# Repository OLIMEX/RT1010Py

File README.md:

# RT10100Py
RT1010Py is Cortex-M7 running at 500Mhz MicroPython board

https://www.olimex.com/Products/MicroPython/RT1010-Py/open-source-hardware

The RT1010-Py can also be used together with its DevKit board 

https://www.olimex.com/Products/MicroPython/RT1010Py-DevKit/open-source-hardware

## Features
* MIMXRT1011DAE5A running at 500Mhz
* 128KB on board RAM
* 2MB SPI Flash
* Three UARTs
* Two hardware SPIs
* Two hardware I2Cs
* One hardware I2S
* Four PWM units with complementary outputs for push-pull drivers
* USB 2.0 OTG
* Micro SD card connector
* RTC with 32.768 kHz crystal
* RESET button
* BOOT button
* UEXT connector with 3.3V, GND, I2C, SPI, and UART
* Two GPIOs headers spaced at 22.86 mm (0.9”)
* Dimensions: (53.34 x 25.4)mm (2.1 x 1)”

## Library

The library must be copied on the MicroPython board before using some of the examples.

### MicroPython MIP Installer

On a WiFi capable plateform:

```
>>> import mip
>>> mip.install("github:OLIMEX/RT1010Py")
```

Or via the mpremote utility :

```
mpremote mip install github:OLIMEX/RT1010Py
```

### Manual installation

Copy all the files from __OLIMEX/RT1010Py/lib__ repository to your MicroPython board under __/lib__ directory.

## Documentation

Check the files in OLIMEX/RT1010Py/__DOCUMENTS__ for ressources:

* [RT101-0Py User Manual](DOCUMENTS/RT1010Py-user-manual.pdf) (pdf)
* [RT1010-Py PinOut](DOCUMENTS/RT1010-py-pinout.jpg) (jpg)
* [RT1010-py board](DOCUMENTS/RT1010-py-board.png) (png, for drawing circuit)
* and some other

Also check the RT1010Py-DevKit user manual at [OLIMEX/RT1010Py-DevKit repository](https://github.com/OLIMEX/RT1010Py-DevKit/tree/main)

## Licensee
* Hardware is released under Apache 2.0 Licensee
* Software is released under GPL3 Licensee
* Documentation is released under CC BY-SA 3.0

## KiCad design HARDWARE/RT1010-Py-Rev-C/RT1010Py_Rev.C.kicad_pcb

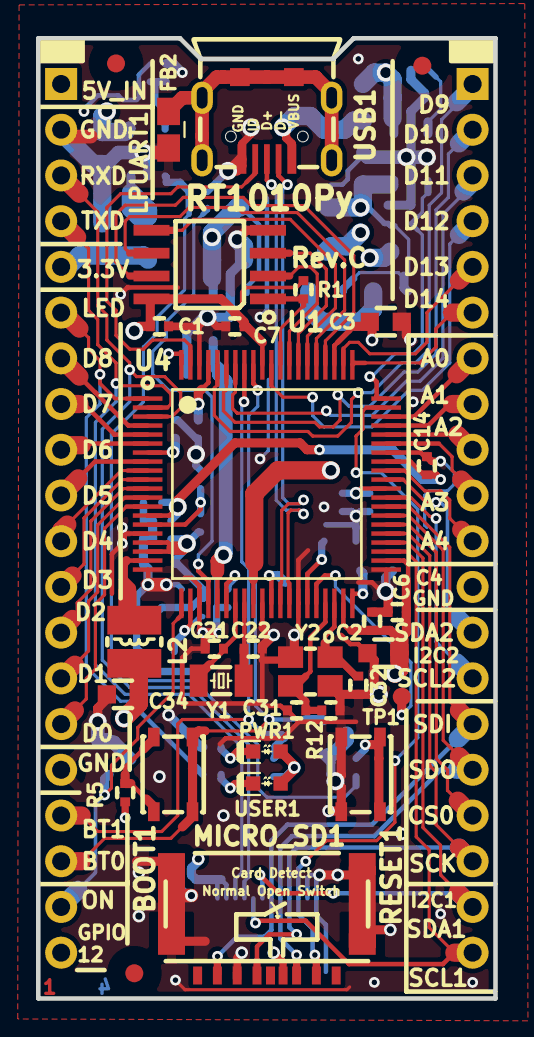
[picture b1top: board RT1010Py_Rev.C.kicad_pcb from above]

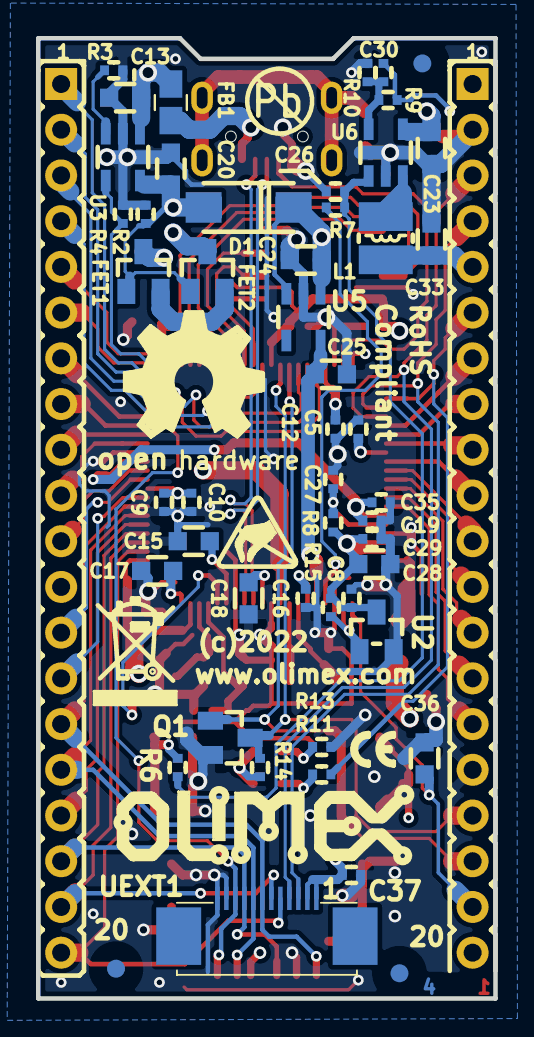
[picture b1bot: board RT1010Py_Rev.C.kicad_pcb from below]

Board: 4 copper layers, 25.4 x 53.3 mm, 89 parts (58 on the bottom side), 77 nets.

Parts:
Anty_Static: Val**; LOGO_ANTISTATIC_SMALL_4.5mmX2.8mm
BOOT1: YTS-A016-X
C1, C8, C37: 100nF/10V/20%/X5R/0402; C_0402_5MIL_DWS
C2, C3, C15, C17, C18, C24, C25, C33: 4.7uF/6.3V/0603; C_0603_5MIL_DWS
C4, C5, C6, C7, C9, C10, C12, C14, C16, C19, C26, C27, C29, C35: 220nF/+80-20%/10VDC/0402; C_0402_5MIL_DWS
C13, C20, C23: 10uF/6.3V/20%/X5R/0603; C_0603_5MIL_DWS
C21, C22, C30: 22pF/NP0/5%/0402; C_0402_5MIL_DWS
C28, C34: 22uF/6.3V/20%/X5R/0603; C_0603_5MIL_DWS
C31, C32: 33pF/50V/5%/C0G/0402; C_0402_5MIL_DWS
C36: NA; C_0603_5MIL_DWS
CON1, CON2: HN1X20; HN1x20
D1: 1N5822/(SS34)/SMA; SMA-KA
FB1, FB2: FB0805/600R/2A; L_0805_5MIL_DWS
FET1, FET2: WPM2015-3/TR; SOT23
FID1, FID2, FID3, FID4, FID5, FID6: Fiducial; Fiducial1x3
L1, L2: 2.2uH/NRS3015T2R2MNGH; CD32
MICRO_SD1: uSD(TFC-9P-1.7H); uSD(TFC-9P-1.xH(ATFFS150A01BR016))
OSH_Logo: LOGO_OPENHARDWARE_8x8
Olimex_Logo: OLIMEX_LOGO_TB
PB_Free: LOGO_PBFREE
PWR1: LED/Yellow/0603; LED_0603_KA
Q1: LMUN2211LT1G; SOT23
R1, R2, R4, R7, R11, R13: 10K/0402; R_0402_5MIL_DWS
R3: 10K/1%; R_0402_5MIL_DWS
R5, R6: 100R/0402; R_0402_5MIL_DWS
R8: 30K/0402; R_0402_5MIL_DWS
R9: 4.99K/1%; R_0402_5MIL_DWS
R10: 1.1K/1%; R_0402_5MIL_DWS
R12: 1M/0402; R_0402_5MIL_DWS
R14: 2.2K/0402; R_0402_5MIL_DWS
R15: 100K/0402; R_0402_5MIL_DWS
RESET1: YTS-A016-X
ReCycle: LOGO_RECYCLEBIN_1
Sign_CE_Small: CE_Sign_Small
TP1: TESTPAD; TP_SMD
U1: EN25QH16B-104HIP; SOIC-8_208mil
U2: VDA2710NTA(SOT-23); SOT-23
U3: SY6280AAC(SOT23-5); SOT-23-5
U4: MIMXRT1011DAE5A; LQFP-80_12x12mm_0.5_mm_pitch
U5: HX6211A332MR; SOT-23-5
U6: SY8089AAAC(SOT23-5); SOT-23-5
UEXT1: FPV-WZB21-12-LF
USB1: MISB-SWMM-5B-LF; USB-MICRO_MISB-SWMM-5B_LF
USER1: LED/Green/0603; LED_0603_KA
Y1: 32.768KHz/12.5pF/2P/1206; CM7V-T1A(Crystal_Package-1206_3.20x1.50x0.65mm)
Y2: 24MHz/20ppm/20pF/4P/3225; TSX-3.2x2.5mm_GND(3)

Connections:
+3V3: C1.1, C2.1, C3.1, C4.1, C5.1, C6.1, C7.1, C8.1, C9.1, C10.1, C28.1, C29.1, C30.1, C33.1, C37.1, CON1.5, L1.2, MICRO_SD1.4, PWR1.2, R1.1, R5.1, R8.2, R9.1, R14.1, R15.1, U1.8, U2.3, U4.7, U4.17, U4.18, U4.39, U4.42, U4.50, U4.63, U4.71, UEXT1.1, UEXT1.2, USER1.2
/5V_USB_OTG: C13.1, FB1.2, FET1.3, U3.1, U4.29
/BOOTSEL0: BOOT1.2, CON1.18, Q1.1, U4.72
/BOOTSEL1: CON1.17, Q1.3, R14.2, U4.73
/BUT_RESET: R6.2, RESET1.2
/GPIO2_IO00: CON2.1, U4.76
/GPIO2_IO01: CON2.2, U4.75
/GPIO2_IO02: CON2.3, U4.74
/GPIO2_IO05: CON2.4, U4.70
/GPIO2_IO12: CON2.5, U4.62
/GPIO2_IO13: CON2.6, U4.61
/GPIO_00: CON1.15, U4.13
/GPIO_01: CON1.14, U4.12
/GPIO_02: CON1.13, U4.11
/GPIO_03: CON1.12, U4.10
/GPIO_04: CON1.11, U4.9
/GPIO_05: CON1.10, U4.8
/GPIO_06: CON1.9, U4.6
/GPIO_07: CON1.8, U4.5
/GPIO_08: CON1.7, U4.4
/GPIO_11_LED: CON1.6, R11.2, U4.1
/GPIO_12: CON1.20, U4.80
/I2C1_SCL: CON2.20, U4.43, UEXT1.5
/I2C1_SDA: CON2.19, U4.44, UEXT1.6
/I2C2_SCL: CON2.14, U4.49
/I2C2_SDA: CON2.13, U4.51
/LPSPI1_PCS0: CON2.10, U4.55
/LPSPI1_PCS1: CON2.7, U4.58
/LPSPI1_SCK: CON2.11, U4.52
/LPSPI1_SDI: CON2.8, U4.57
/LPSPI1_SDO: CON2.9, U4.56
/LPSPI2_PCS0: CON2.17, U4.46
/LPSPI2_PCS1: MICRO_SD1.2, U4.59, UEXT1.10
/LPSPI2_SCK: CON2.18, MICRO_SD1.5, U4.45, UEXT1.9
/LPSPI2_SDI: CON2.15, MICRO_SD1.7, U4.48, UEXT1.7
/LPSPI2_SDO: CON2.16, MICRO_SD1.3, U4.47, UEXT1.8
/LPUART1_RXD: CON1.3, U4.3, UEXT1.4
/LPUART1_TXD: CON1.4, U4.2, UEXT1.3
/QF_CLK: U1.6, U4.65
/QF_D0: U1.5, U4.66
/QF_D1: U1.2, U4.68
/QF_D2: U1.3, U4.67
/QF_D3: U1.7, U4.64
/QF_SS: R1.2, U1.1, U4.69
/USB_OTG1_ID: U4.79, USB1.4
/USB_OTG1_PWR: R4.1, U3.4, U4.60
/USB_OTG_DN: U4.32, USB1.2
/USB_OTG_DP: U4.33, USB1.3
/VDD_USB_3V: C18.1, U4.31
/nRESET: R15.2, U2.1, U4.22
EXT_5V_IN: C20.1, CON1.1, D1.2, FET1.1, FET2.1, R2.2, U3.5
GND: C1.2, C2.2, C3.2, C4.2, C5.2, C6.2, C7.2, C8.2, C9.2, C10.2, C12.2, C13.2, C14.2, C15.2, C16.2, C17.2, C18.2, C19.2, C20.2, C21.2, C22.2, C23.2, C24.2, C25.2, C26.2, C27.2, C28.2, C29.2, C31.1, C32.1, C33.2, C34.2, C35.2, C36.2, C37.2, CON1.2, CON1.16, CON2.12, FB2.2, MICRO_SD1.6, MICRO_SD1.CH1, Q1.2, R2.1, R3.2, R4.2, R10.2, R12.2, R13.2, RESET1.1, U1.4, U2.2, U3.2, U4.16, U4.20, U4.23, U4.30, U4.34, U4.41, U4.54, U4.78, U5.2, U6.2, UEXT1.11, UEXT1.12, USB1.5, Y2.3
unnamed: BOOT1.1, R5.2
unnamed: C12.1, C14.1, C19.1, C34.1, C35.1, L2.2, U4.14, U4.53, U4.77
unnamed: C15.1, U4.35
unnamed: C16.1, U4.26
unnamed: C17.1, U4.40
unnamed: C21.1, U4.27, Y1.1
unnamed: C22.1, U4.28, Y1.2
unnamed: C23.1, C24.1, D1.1, FET2.3, U5.1, U5.3, U6.4
unnamed: C26.1, R6.1, R7.2, U6.1
unnamed: C27.1, R8.1, U4.15
unnamed: C30.2, R9.2, R10.1, U6.5
unnamed: C31.2, R12.1, U4.37, Y2.2
unnamed: C32.2, U4.38, Y2.1
unnamed: FB1.1, USB1.1
unnamed: FB2.1, USB1.0
unnamed: FET1.2, FET2.2
unnamed: L1.1, U6.3
unnamed: L2.1, U4.19
unnamed: PWR1.1, R13.1
unnamed: R3.1, U3.3
unnamed: R11.1, USER1.1
unnamed: TP1.1, U4.36
ON_OFF: C36.1, CON1.19, U4.21
PMIC_ONREQ: R7.1, U4.24
VDD_SVNS: C25.1, U4.25, U5.5

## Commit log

2023-10-23 initial upload
2023-10-31 update user manual
2023-10-31 add software
2023-11-08 user manual update
2025-04-03 add usbtinyuf2 info
2025-10-13 Add examples, update documentation
2025-10-24 Fix typo. Update UEXT & fUEXT graphics. Install RT1010Py libraries. Append WS2812/NeoPixel support
2025-10-25 Install the machine version! Not the pyboard one

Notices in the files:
HARDWARE/RT1010-Py-Rev-C/RT1010Py_Rev.C.kicad_pcb:
(c)2022
